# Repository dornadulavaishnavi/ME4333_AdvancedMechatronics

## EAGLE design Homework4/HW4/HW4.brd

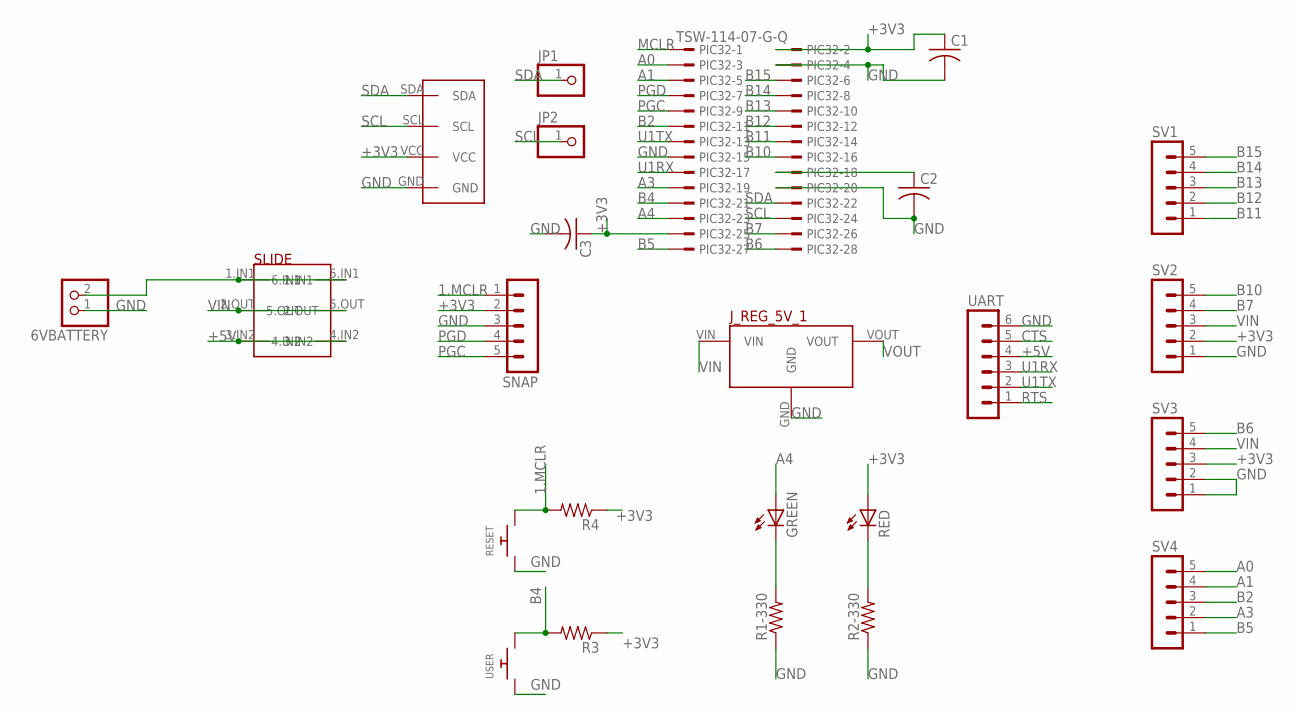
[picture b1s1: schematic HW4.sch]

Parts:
6VBATTERY: PINHD-1X2; 1X02
C1, C2, C3: C-US025-025X050; C025-025X050
GREEN: LED3MM
JP1, JP2: PINHD-1X1; 1X01
J_REG_5V_1: 5V_VOLTAGE_REGULATOR
PIC32: TSW-114-07-G-Q; TSW-114-XX-G-Q
R1-330, R2-330, R3, R4: R-US_0204/7; 0204/7
RED: LED3MM
RESET: SWITCH_PUSHBUTTONSOFTTOUCHSMD_SJ; PUSHBUTTON_SMD_SJ
SLIDE: SLIDE_DEVICE; SLIDE_FOOTPRINT
SNAP: MA05-1
SV1, SV2, SV3, SV4: MA05-1
U$1: SSD1306_DEVICE; SSD1306_FOOTPRINT
UART: MA06-1
USER: SWITCH_PUSHBUTTONSOFTTOUCHSMD_SJ; PUSHBUTTON_SMD_SJ

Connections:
1.MCLR: R4.2, RESET.P$2, SNAP.1
+3V3: C1.1, C3.1, PIC32.2, PIC32.25, R3.1, R4.1, RED.A, SNAP.2, SV2.2, SV3.3, U$1.VCC
+5V: SLIDE.3.IN2, SLIDE.4.IN2, UART.4
A0: PIC32.3, SV4.5
A1: PIC32.5, SV4.4
A3: PIC32.19, SV4.2
A4: GREEN.A, PIC32.23
B2: PIC32.11, SV4.3
B4: PIC32.21, R3.2, USER.P$2
B5: PIC32.27, SV4.1
B6: PIC32.28, SV3.5
B7: PIC32.26, SV2.4
B10: PIC32.16, SV2.5
B11: PIC32.14, SV1.1
B12: PIC32.12, SV1.2
B13: PIC32.10, SV1.3
B14: PIC32.8, SV1.4
B15: PIC32.6, SV1.5
CTS: UART.5
GND: 6VBATTERY.1, C1.2, C2.2, C3.2, J_REG_5V_1.GND, PIC32.4, PIC32.15, PIC32.20, R1-330.1, R2-330.1, RESET.P$1, SNAP.3, SV2.1, SV3.1, SV3.2, U$1.GND, UART.6, USER.P$1
MCLR: PIC32.1
unnamed: 6VBATTERY.2, SLIDE.1.IN1, SLIDE.5.IN1 (6.IN1)
unnamed: GREEN.K (C), R1-330.2
unnamed: R2-330.2, RED.K (C)
unnamed: C2.1, PIC32.18
PGC: PIC32.9, SNAP.5
PGD: PIC32.7, SNAP.4
RTS: UART.1
SCL: JP2.1, PIC32.24, U$1.SCL
SDA: JP1.1, PIC32.22, U$1.SDA
U1RX: PIC32.17, UART.3
U1TX: PIC32.13, UART.2
VIN: J_REG_5V_1.VIN, SLIDE.2.OUT, SLIDE.5.OUT, SV2.3, SV3.4
VOUT: J_REG_5V_1.VOUT

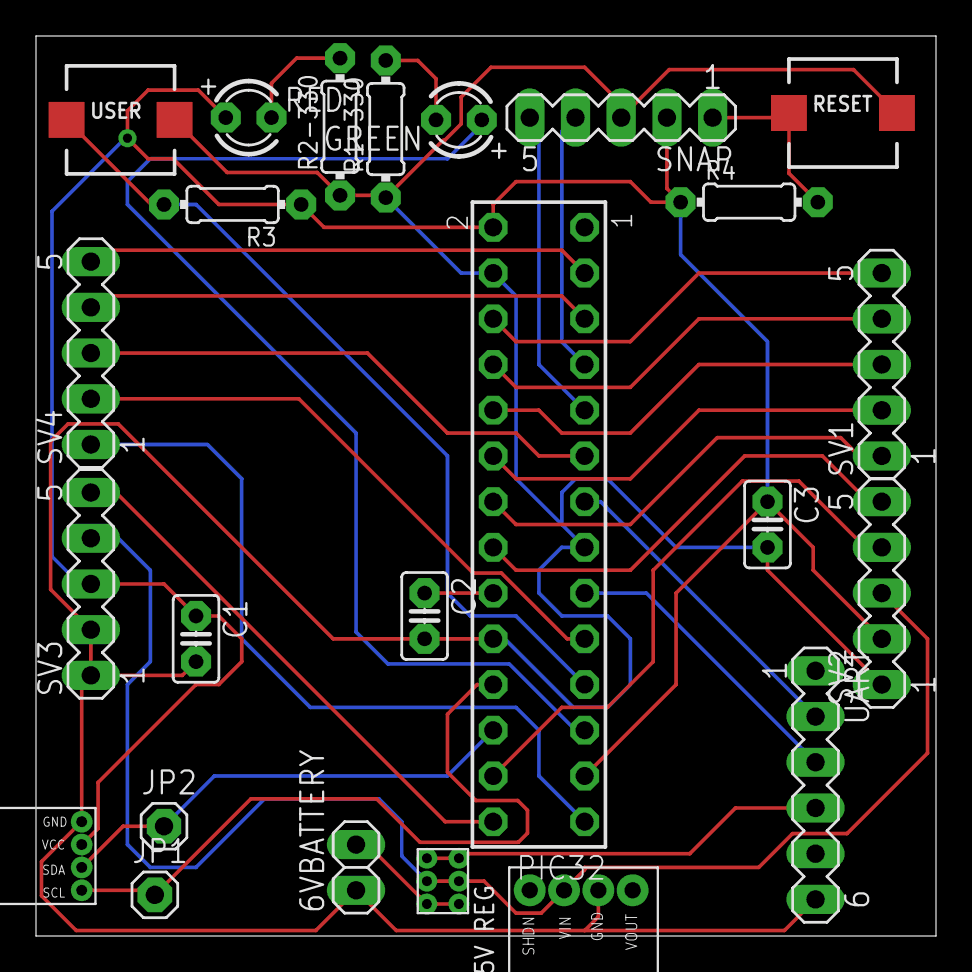
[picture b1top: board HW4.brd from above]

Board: 2 copper layers, 50.0 x 50.0 mm, 24 parts (0 on the bottom side), 30 nets.

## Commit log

2022-04-05 adding main for blinking led
2022-04-05 adding images for circuit
2022-04-05 added homework3 folder
2022-04-06 added uart and main code
2022-04-06 everything working, adding circuit image
2022-04-10 schematics+board completed
2022-04-14 created HW5 folder and added spi folders
2022-04-17 spi communication confirmed working, now will be changing to use functions
2022-04-17 got images of both triangle and sin waves
2022-04-20 set up code to test, have questions for OH
2022-04-20 heartbeat blinks
2022-04-20 done at the end of office hours! :)
2022-04-21 starting imu homework 6
2022-04-21 added needed files
2022-04-21 code template set up, will wire sensor and then come back to code
2022-04-21 pushing changes from class
2022-04-22 need to hook up to board and test who_am_i before moving forward
2022-04-24 continuing to debug complimentary filter
2022-04-24 phi and theta are being calculated correctly
2022-04-24 working and recorded! just need to comment and submit
2022-04-24 done! :)
2022-04-27 turns on 1 pixel on screen and led blinks
2022-04-27 draw char written but only printing m
2022-04-28 draw char works
2022-04-28 drawstring function works
2022-04-28 code commented and fps prints
2022-04-28 corrected to print on the line below :)
2022-04-29 circuit wired and code base set up
2022-04-30 leds all light up, seem like the same color though
2022-04-30 functions giving correct output when testing with prints
2022-04-30 changed cycle time to get color
2022-04-30 all leds can turn on with different color
2022-04-30 had to tweak the cycle times, but works! :)
2022-04-30 added image of circuit
2022-05-11 hello world runs over mu serial
2022-05-11 summing sin functions
2022-05-14 first sample code works
2022-05-14 color camera image taken
2022-05-15 takes black and white image
2022-05-15 is partially black and white, partially color
2022-05-15 only row 7 has color
2022-05-15 only rows 7, 14, and 21 are colored
2022-05-15 images uploaded! :)
2022-06-08 Final Project Assembly and CAD
2022-06-09 with a full high threshold, locates center
2022-06-09 with threshold, straight works
2022-06-09 says left, right, or straight based on tape
2022-06-09 camera detects where to turn but motor driver not outputting high enough voltage
2022-06-09 motors turn on now that hbridge is fixed
2022-06-09 pwm running on red wheel
2022-06-09 both motors running on separate pwms
2022-06-09 bluetooth responds with hc name
2022-06-09 bluetooth communication with adafruit friend working
2022-06-09 pico sends proportional error to bluetooth
2022-06-09 final push
